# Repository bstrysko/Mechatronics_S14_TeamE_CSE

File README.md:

Mechatronics_S14_TeamE_CSE
==========================

Spring 2014 Mechatronics Team E Project

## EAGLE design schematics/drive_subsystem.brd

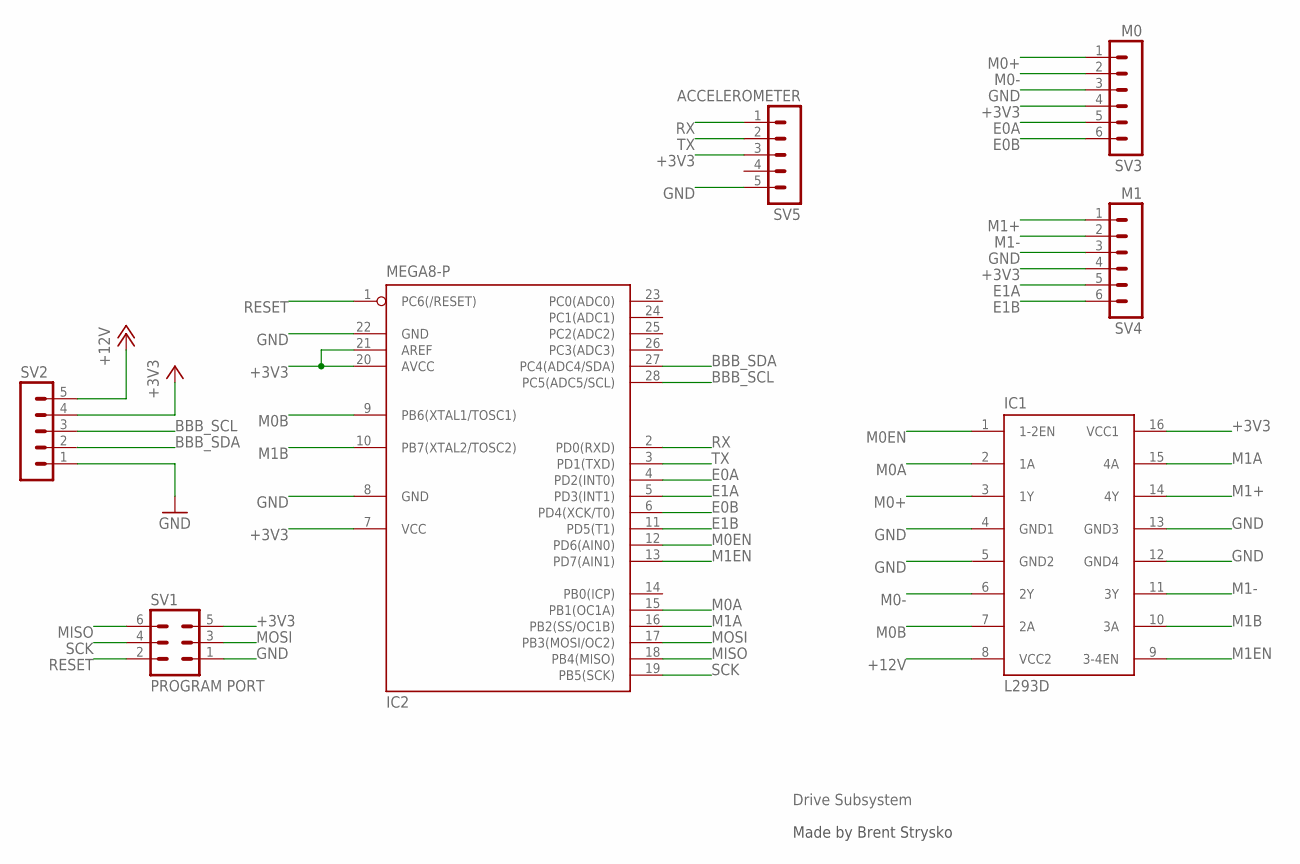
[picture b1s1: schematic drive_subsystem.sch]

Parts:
IC1: L293D; DIL16
IC2: MEGA8-P; DIL28-3
SV1: PROGRAM PORT; MA03-2
SV2: MA05-1
SV3: M0; MA06-1
SV4: M1; MA06-1
SV5: ACCELEROMETER; MA05-1

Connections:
+3V3: IC1.16 (VCC1), IC2.7 (VCC), IC2.20 (AVCC), IC2.21 (AREF), SV1.5, SV2.4, SV3.4, SV4.4, SV5.3
+12V: IC1.8 (VCC2), SV2.5
BBB_SCL: IC2.28 (PC5(ADC5/SCL)), SV2.3
BBB_SDA: IC2.27 (PC4(ADC4/SDA)), SV2.2
E0A: IC2.4 (PD2(INT0)), SV3.5
E0B: IC2.6 (PD4(XCK/T0)), SV3.6
E1A: IC2.5 (PD3(INT1)), SV4.5
E1B: IC2.11 (PD5(T1)), SV4.6
GND: IC1.4 (GND1), IC1.5 (GND2), IC1.12 (GND4), IC1.13 (GND3), IC2.8 (GND), IC2.22 (GND), SV1.1, SV2.1, SV3.3, SV4.3, SV5.5
M0+: IC1.3 (1Y), SV3.1
M0-: IC1.6 (2Y), SV3.2
M0A: IC1.2 (1A), IC2.15 (PB1(OC1A))
M0B: IC1.7 (2A), IC2.9 (PB6(XTAL1/TOSC1))
M0EN: IC1.1 (1-2EN), IC2.12 (PD6(AIN0))
M1+: IC1.14 (4Y), SV4.1
M1-: IC1.11 (3Y), SV4.2
M1A: IC1.15 (4A), IC2.16 (PB2(SS/OC1B))
M1B: IC1.10 (3A), IC2.10 (PB7(XTAL2/TOSC2))
M1EN: IC1.9 (3-4EN), IC2.13 (PD7(AIN1))
MISO: IC2.18 (PB4(MISO)), SV1.6
MOSI: IC2.17 (PB3(MOSI/OC2)), SV1.3
RESET: IC2.1 (PC6(/RESET)), SV1.2
RX: IC2.2 (PD0(RXD)), SV5.1
SCK: IC2.19 (PB5(SCK)), SV1.4
TX: IC2.3 (PD1(TXD)), SV5.2

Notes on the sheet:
Made by Brent Strysko
Drive Subsystem

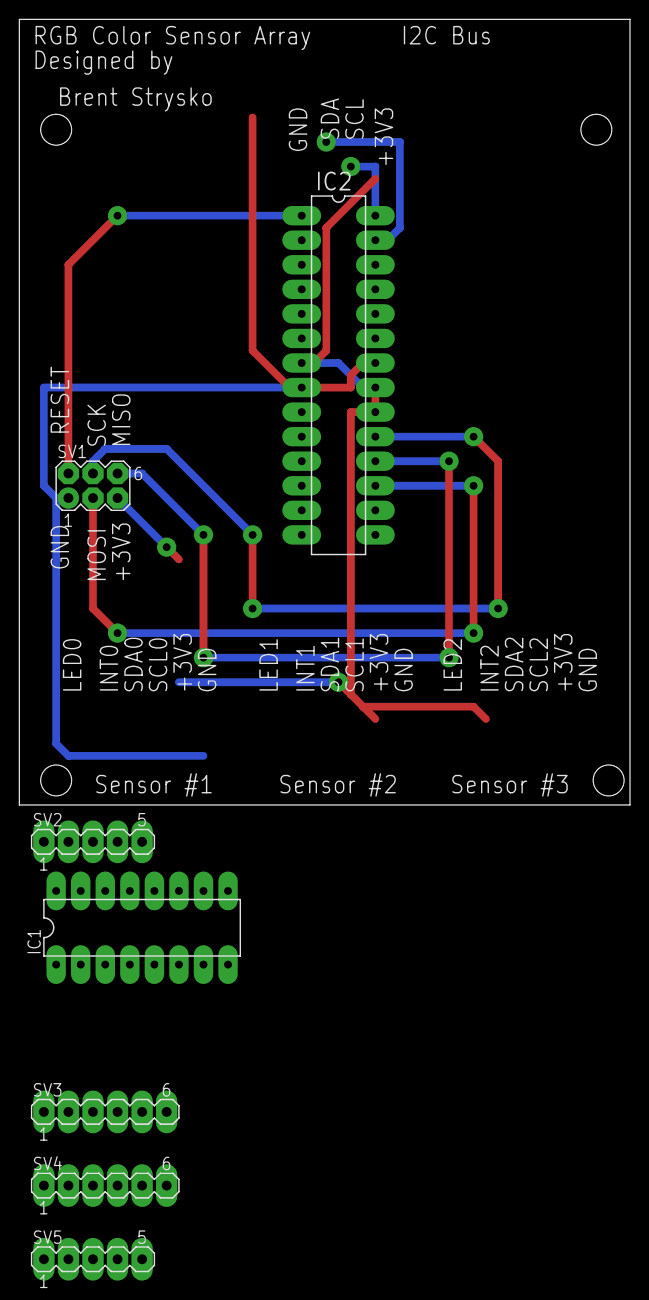
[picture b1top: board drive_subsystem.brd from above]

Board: 2 copper layers, 63.2 x 81.3 mm, 7 parts (0 on the bottom side), 25 nets.

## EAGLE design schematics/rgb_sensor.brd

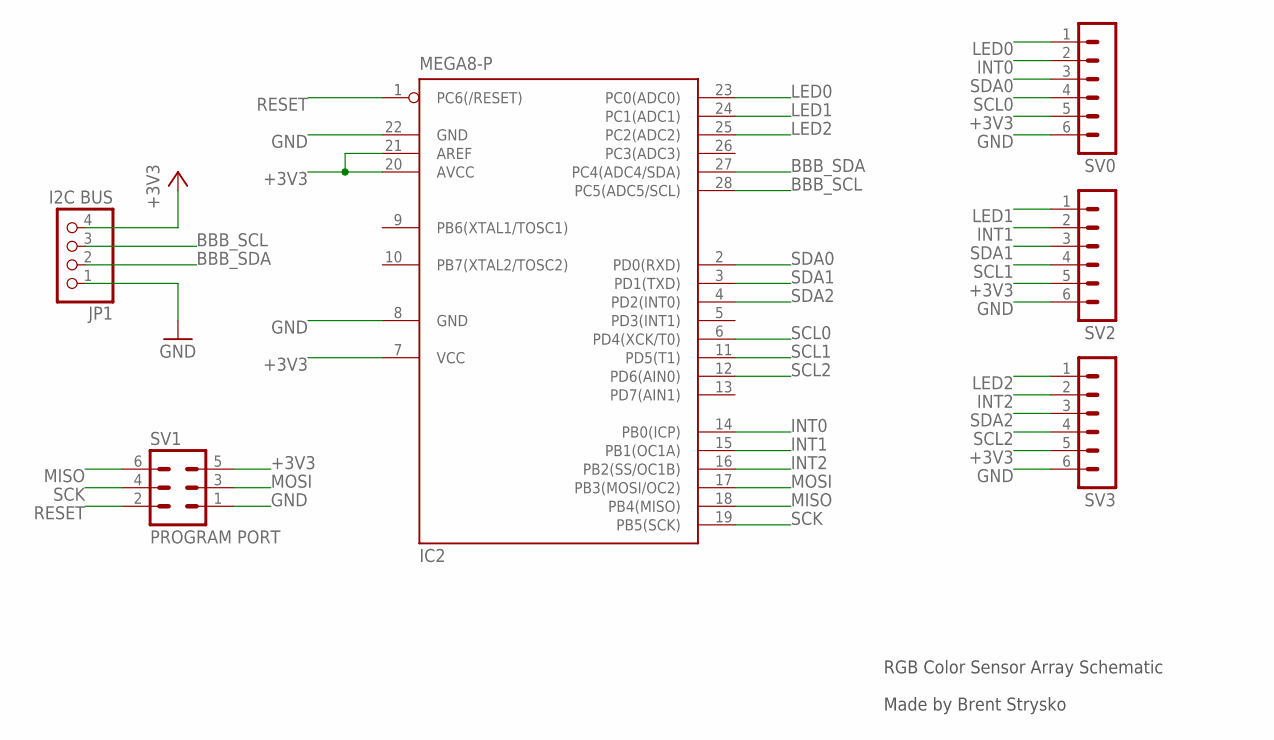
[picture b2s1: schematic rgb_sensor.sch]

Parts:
IC2: MEGA8-P; DIL28-3
JP1: I2C BUS; 1X04
SV0, SV2, SV3: MA06-1
SV1: PROGRAM PORT; MA03-2

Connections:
+3V3: IC2.7 (VCC), IC2.20 (AVCC), IC2.21 (AREF), JP1.4, SV0.5, SV1.5, SV2.5, SV3.5
BBB_SCL: IC2.28 (PC5(ADC5/SCL)), JP1.3
BBB_SDA: IC2.27 (PC4(ADC4/SDA)), JP1.2
GND: IC2.8 (GND), IC2.22 (GND), JP1.1, SV0.6, SV1.1, SV2.6, SV3.6
INT0: IC2.14 (PB0(ICP)), SV0.2
INT1: IC2.15 (PB1(OC1A)), SV2.2
INT2: IC2.16 (PB2(SS/OC1B)), SV3.2
LED0: IC2.23 (PC0(ADC0)), SV0.1
LED1: IC2.24 (PC1(ADC1)), SV2.1
LED2: IC2.25 (PC2(ADC2)), SV3.1
MISO: IC2.18 (PB4(MISO)), SV1.6
MOSI: IC2.17 (PB3(MOSI/OC2)), SV1.3
RESET: IC2.1 (PC6(/RESET)), SV1.2
SCK: IC2.19 (PB5(SCK)), SV1.4
SCL0: IC2.6 (PD4(XCK/T0)), SV0.4
SCL1: IC2.11 (PD5(T1)), SV2.4
SCL2: IC2.12 (PD6(AIN0)), SV3.4
SDA0: IC2.2 (PD0(RXD)), SV0.3
SDA1: IC2.3 (PD1(TXD)), SV2.3
SDA2: IC2.4 (PD2(INT0)), SV3.3

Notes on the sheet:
RGB Color Sensor Array Schematic
Made by Brent Strysko

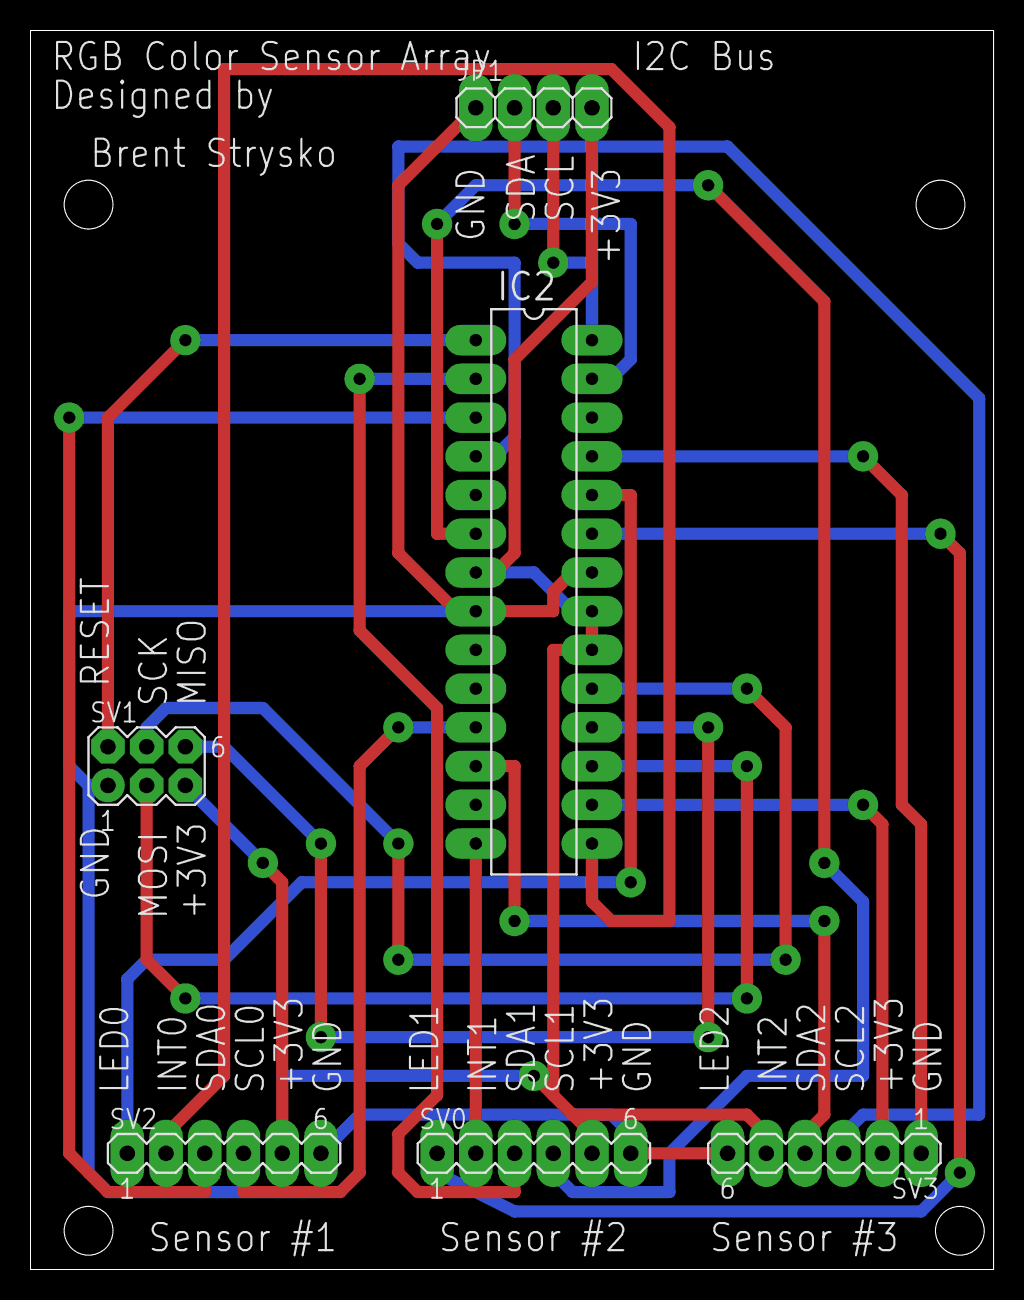
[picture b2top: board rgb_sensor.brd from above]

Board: 2 copper layers, 63.2 x 81.3 mm, 6 parts (0 on the bottom side), 20 nets.

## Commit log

2014-01-28 Created basic high level headers for different subsystems of design
2014-01-29 Redesigned part of high level API and declared more functions. Started implementing Explorer class.
2014-01-31 Able to move in grid like manner while sensing
2014-02-01 Began creating web interface in web_root
2014-02-01 Fixed negative y axis issue when passing defect location to client
2014-02-01 Create gh-pages branch via GitHub
2014-02-01 Got DC motor working. Besides possible bug for demo this afternoon commit for Motor Lab
2014-02-02 Removed schematics since Drive Subsystem and RGB Color Sensor Array each now have their own repositories
2014-02-02 Moved beaglebone black to top folder since BeagleBoneBlack code is the primary material that will exist in this repository.
2014-02-03 Fixed undefined errors. Began implementing Camera framework
2014-02-03 Implemented Frame heiarchy
2014-02-03 Rudementary hard coded RGB color detection coded
2014-02-06 Removed old arduino code from motor lab
2014-02-09 Created the application class window. Added histogram code to main.cpp . Created efficient Makefile system.
2014-02-09 Implemented binary red color detection using fixed # of contours. Horrible solution but it works. Need to implement better algorithm after I2C code is written.
2014-02-09 Moved I2C code to individual folder. Have basic functionality working for I2C Device. Read only implemented, not write. Still need to test.
2014-02-09 Implemented i2c device write function
2014-02-10 Implemented servo functionality for drive system(Motor Lab)
2014-02-10 Created Arduino library to communicate with BeagleboneBlack over I2C
2014-02-10 Created application class to abstract away program details. Project code now lives in project.cpp. src/main.cpp just initializes project
2014-02-10 Created support in window class for trackbars and multiple image rendering in one window.
2014-02-11 Implemented TextFrames. Color classifier now simply counts the # thresholded pixels.
2014-02-11 Began motor lab Arduino code
2014-02-11 Added support for motors and sensors
2014-02-11 Arduino Code for added motors and sensors
2014-02-12 Previous commit Arduino code
2014-02-14 Removed I2CDevice and left install note to use WireDevice instead. Still need to update dependencies in motor lab
2014-02-14 Modified MotorLab.ino code to work with WireDevice library and added INSTALL instructions for Arduino projects
2014-02-14 Fixed Makefile to delete *.dep on clean. Removed include/i2c/ and src/i2c/ code as project will now be using I2CMaster as explain in BUILD
2014-02-15 Basic single RGB Color Sensor functionality in RGBSensor class. Still need to test on hardware
2014-02-16 Able to read values from RGB Sensor through RGBSensor class
2014-02-16 Initial RGB Sensor schematic and board commits
2014-02-19 Removed no longer used motor lab code from project.cpp and added support to Color such that it can be directly converted to a string
2014-02-19 Added required header to top of every source file in beagleboneblack/
2014-02-26 RGB Color Sensor Array Board Finalized to be Printed
2014-02-26 Drive subsystem schematic without distance sensor support
2014-04-04 Tweaked some parameters so video can be streamed faster over wireless connection
2014-04-09 Integrated RGBColorSensorArray functionality
2014-04-09 Implemented drive system communication support. Removed old motor lab code that was in drive system
2014-04-09 Basic board
2014-04-15 Changed Drive Subsystem to send uint8_ts over the I2C bus instead of doubles
2014-04-16 Code now supports desired point detection and communication code integrated
2014-04-16 Now display current position on GUI and deleted web root
2014-04-16 Now using DriveSubsystem class from repository as opposed to local definition. Deleted local definition
2014-04-16 Now using VisualCSEDefectDetector library
2014-04-16 Tweaked camera size
2014-04-21 Integrated new coms, drive, and began autonomous code
2014-04-22 Working Project for Final Demo #1 Tomorrow!
